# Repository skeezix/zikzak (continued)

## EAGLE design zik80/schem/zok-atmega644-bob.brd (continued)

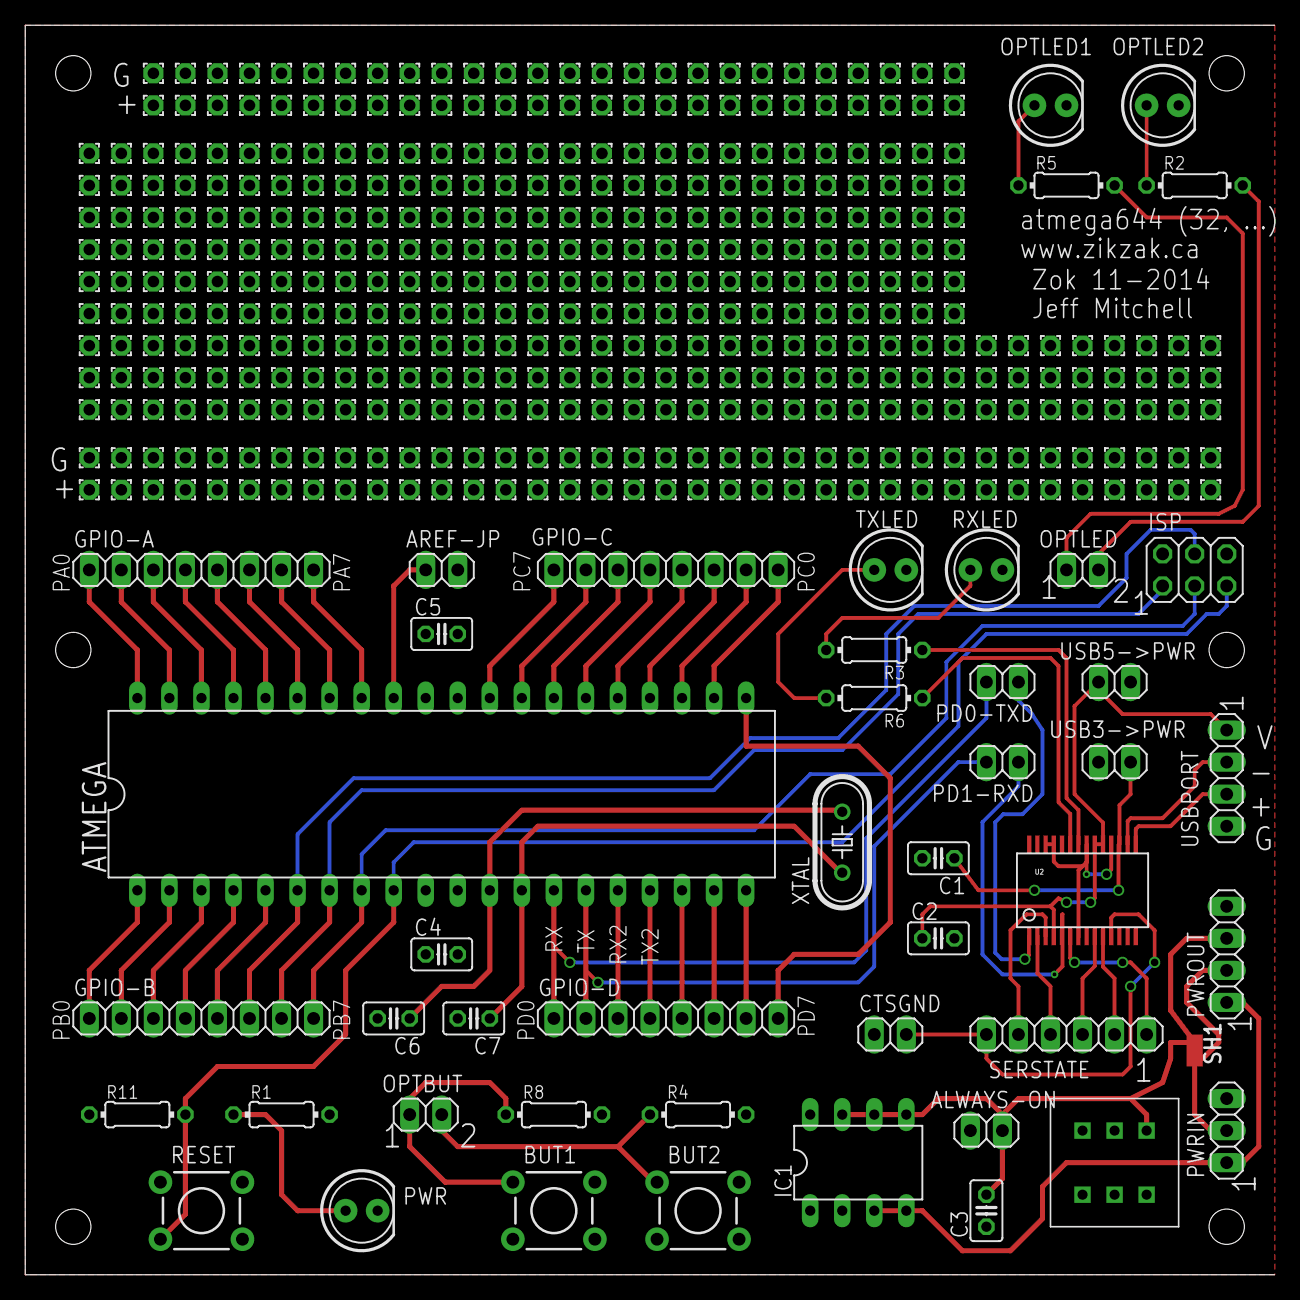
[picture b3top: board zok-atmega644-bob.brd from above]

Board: 2 copper layers, 99.1 x 99.1 mm, 447 parts (0 on the bottom side), 64 nets.

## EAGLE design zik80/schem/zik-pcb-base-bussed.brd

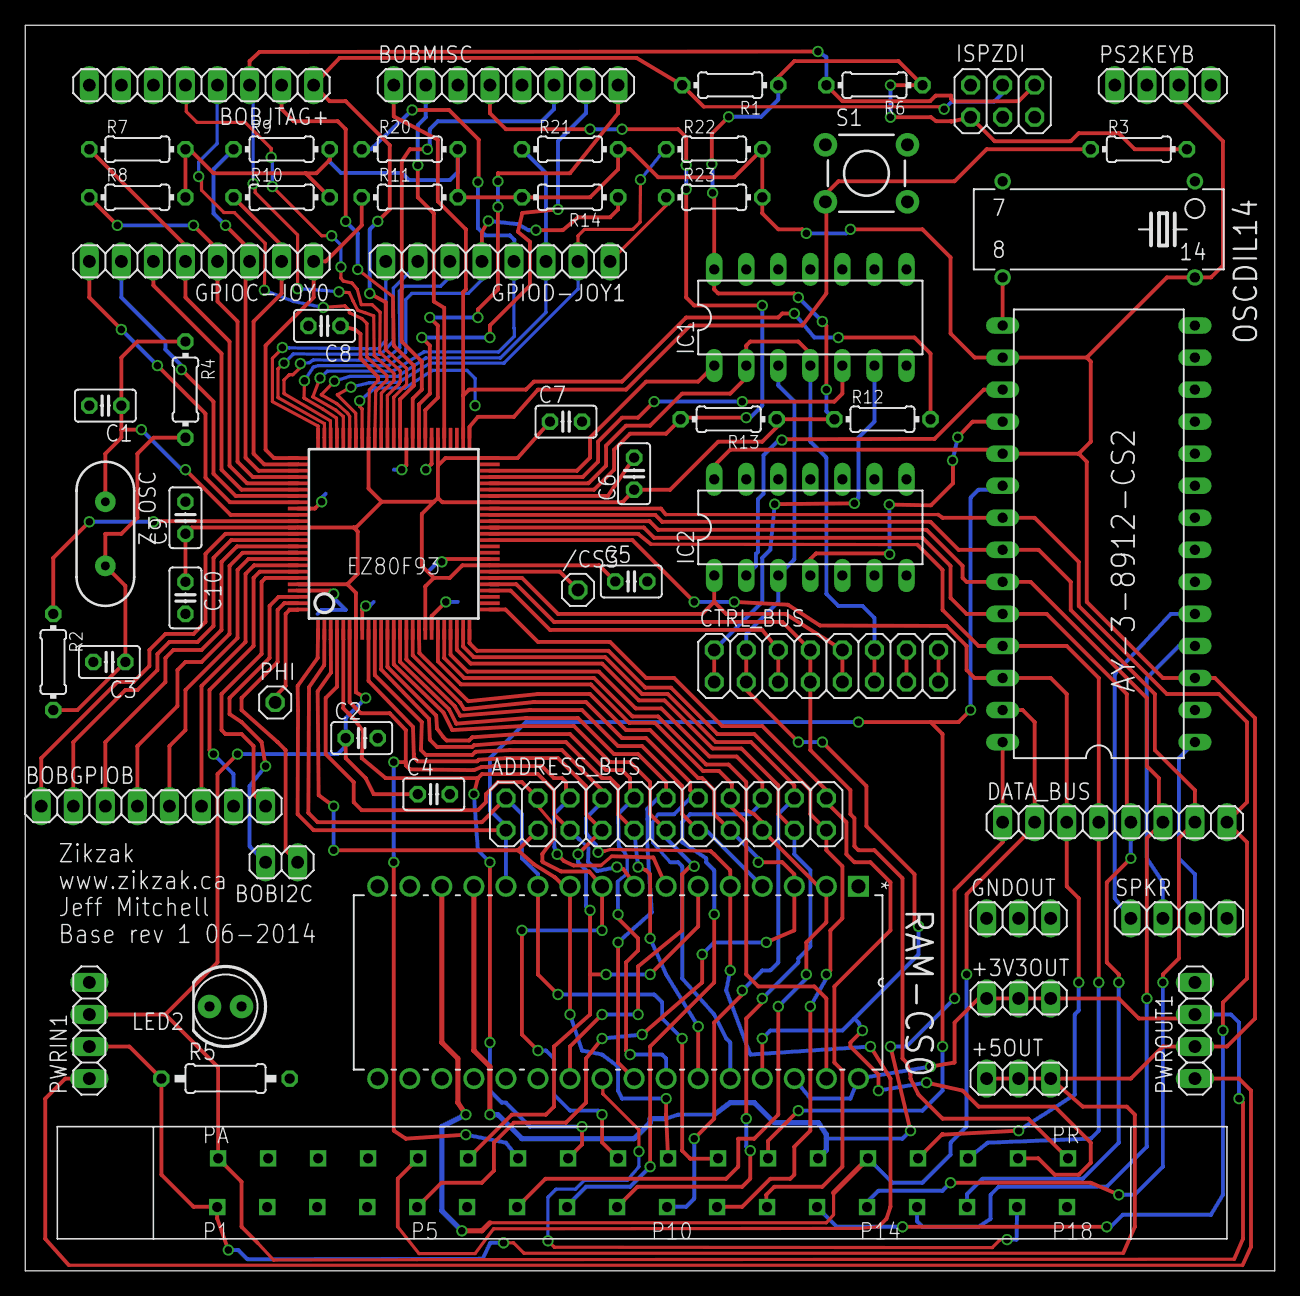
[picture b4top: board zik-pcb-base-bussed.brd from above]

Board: 2 copper layers, 99.0 x 98.7 mm, 57 parts (0 on the bottom side), 94 nets.

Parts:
+3V3OUT, +5OUT: 1X03
/CS3: 1X01
ADDRESS_BUS: 2X11
AY-3-8912-CS2: DIL28
BOBGPIOB: 1X08
BOBI2C: 1X02
BOBJTAG+: 1X08
BOBMISC: 1X08
C1, C3: 22pF; C025-025X050
C2, C4, C5, C6, C7, C8, C9, C10: .1uF; C025-025X050
CART-CS1: ZIKCART36; ZIKCARTSLOT
CTRL_BUS: 2X08
DATA_BUS: 1X08
EZ80F93: SQFP-S-14X14-100
GNDOUT: 1X03
GPIOC-JOY0: 1X08
GPIOD-JOY1: 1X08
IC1: 7432N; DIL14
IC2: 7404N; DIL14
ISPZDI: 2X03
LED2: LED5MM
OSCDIL14: 2.5MHz; SG51
PHI: 1X01
PS2KEYB: 1X04
PWRIN1: 1X04
PWROUT1: 1X04
R1, R3, R6, R7, R8, R9, R10, R11, R12, R13, R14, R20, R21, R22, R23: 10K; 0204/7
R2: 220 O; 0204/7
R4: 100K; 0204/7
R5: 1K; 0207/10
RAM-CS0: AS6C1008-55PCN; DIP254P1524X393-32
S1: SWITCH-MOMENTARY-2PTH; TACTILE-PTH
SPKR: 1X04
Z-OSC: 20Mhz; HC49US

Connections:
+3V3: +3V3OUT.1, +3V3OUT.2, +3V3OUT.3, C2.1, C4.1, C5.1, C6.1, C7.1, C8.1, C9.1, C10.1, CART-CS1.PA, EZ80F93.7, EZ80F93.18, EZ80F93.33, EZ80F93.43, EZ80F93.50, EZ80F93.56, EZ80F93.67, EZ80F93.87, EZ80F93.96, IC1.14, ISPZDI.1, PWRIN1.3, PWROUT1.3, R1.1, R3.2, R6.1, R12.1, R13.1, RAM-CS0.30, RAM-CS0.32
+5V: +5OUT.1, +5OUT.2, +5OUT.3, AY-3-8912-CS2.3, AY-3-8912-CS2.16, AY-3-8912-CS2.19, CART-CS1.P1, IC2.14, OSCDIL14.14, PS2KEYB.3, PWRIN1.2, PWROUT1.2, R5.1, R7.2, R8.2, R9.2, R10.2, R11.2, R14.2, R20.2, R21.2, R22.2, R23.2
+CS2: AY-3-8912-CS2.17, IC2.2
+MEMWRITE: AY-3-8912-CS2.18, IC2.4
/BUSACK: CTRL_BUS.15, CTRL_BUS.16, EZ80F93.54
/BUSREQ: CTRL_BUS.13, CTRL_BUS.14, EZ80F93.53
/CS0: CTRL_BUS.5, CTRL_BUS.6, EZ80F93.29, RAM-CS0.22
/CS1: CART-CS1.PR, CTRL_BUS.7, CTRL_BUS.8, EZ80F93.30
/CS2: CTRL_BUS.9, CTRL_BUS.10, EZ80F93.31, IC2.1
/CS3: /CS3.1, EZ80F93.32
/IOREQ: BOBMISC.4, EZ80F93.45, R13.2
/MEMREAD: CART-CS1.P17, CTRL_BUS.1, CTRL_BUS.2, IC1.6, RAM-CS0.24
/MEMWRITE: CART-CS1.PQ, CTRL_BUS.3, CTRL_BUS.4, IC1.3, IC2.3, RAM-CS0.29
/MREQ: CTRL_BUS.11, CTRL_BUS.12, EZ80F93.46, IC1.2, IC1.4
/RD: EZ80F93.47, IC1.5
/WR: EZ80F93.48, IC1.1
A0: ADDRESS_BUS.1, AY-3-8912-CS2.20, CART-CS1.PL, EZ80F93.1, RAM-CS0.12
A1: ADDRESS_BUS.2, CART-CS1.PK, EZ80F93.2, RAM-CS0.11
A2: ADDRESS_BUS.3, CART-CS1.PJ, EZ80F93.3, RAM-CS0.10
A3: ADDRESS_BUS.4, CART-CS1.PI, EZ80F93.4, RAM-CS0.9
A4: ADDRESS_BUS.5, CART-CS1.PH, EZ80F93.5, RAM-CS0.8
A5: ADDRESS_BUS.6, CART-CS1.PG, EZ80F93.6, RAM-CS0.7
A6: ADDRESS_BUS.7, CART-CS1.PF, EZ80F93.9, RAM-CS0.6
A7: ADDRESS_BUS.8, CART-CS1.PE, EZ80F93.10, RAM-CS0.5
A8: ADDRESS_BUS.9, CART-CS1.PD, EZ80F93.11, RAM-CS0.27
A9: ADDRESS_BUS.10, CART-CS1.PC, EZ80F93.12, RAM-CS0.26
A10: ADDRESS_BUS.11, CART-CS1.PB, EZ80F93.13, RAM-CS0.23
A11: ADDRESS_BUS.12, CART-CS1.P2, EZ80F93.14, RAM-CS0.25
A12: ADDRESS_BUS.13, CART-CS1.P3, EZ80F93.15, RAM-CS0.4
A13: ADDRESS_BUS.14, CART-CS1.P4, EZ80F93.16, RAM-CS0.28
A14: ADDRESS_BUS.15, CART-CS1.P5, EZ80F93.17, RAM-CS0.3
A15: ADDRESS_BUS.16, CART-CS1.P6, EZ80F93.20, RAM-CS0.31
A16: ADDRESS_BUS.17, CART-CS1.P7, EZ80F93.21, RAM-CS0.2
A17: ADDRESS_BUS.18, CART-CS1.P8, EZ80F93.22
A18: ADDRESS_BUS.19, CART-CS1.P9, EZ80F93.23
A19: ADDRESS_BUS.20, CART-CS1.P10, EZ80F93.24
A20: ADDRESS_BUS.21, CART-CS1.P11, EZ80F93.25
A21: ADDRESS_BUS.22, CART-CS1.P12, EZ80F93.26
D0: AY-3-8912-CS2.28, CART-CS1.PM, DATA_BUS.1, EZ80F93.35, RAM-CS0.13
D1: AY-3-8912-CS2.27, CART-CS1.PN, DATA_BUS.2, EZ80F93.36, RAM-CS0.14
D2: AY-3-8912-CS2.26, CART-CS1.PO, DATA_BUS.3, EZ80F93.37, RAM-CS0.15
D3: AY-3-8912-CS2.25, CART-CS1.PP, DATA_BUS.4, EZ80F93.38, RAM-CS0.17
D4: AY-3-8912-CS2.24, CART-CS1.P16, DATA_BUS.5, EZ80F93.39, RAM-CS0.18
D5: AY-3-8912-CS2.23, CART-CS1.P15, DATA_BUS.6, EZ80F93.40, RAM-CS0.19
D6: AY-3-8912-CS2.22, CART-CS1.P14, DATA_BUS.7, EZ80F93.41, RAM-CS0.20
D7: AY-3-8912-CS2.21, CART-CS1.P13, DATA_BUS.8, EZ80F93.42, RAM-CS0.21
GND: AY-3-8912-CS2.6, C1.2, C2.2, C3.2, C4.2, C5.2, C6.2, C7.2, C8.2, C9.2, C10.2, CART-CS1.P18, EZ80F93.8, EZ80F93.19, EZ80F93.34, EZ80F93.44, EZ80F93.57, EZ80F93.61, EZ80F93.84, EZ80F93.97, GNDOUT.1, GNDOUT.2, GNDOUT.3, IC1.7, IC1.9, IC1.10, IC1.12, IC1.13, IC2.5, IC2.7, IC2.9, IC2.11, IC2.13, ISPZDI.3, ISPZDI.5, LED2.K, OSCDIL14.7, PS2KEYB.2, PWRIN1.4, PWROUT1.4, RAM-CS0.16, S1.1, SPKR.4
HALT_SLP: BOBMISC.2, EZ80F93.55
unnamed: C3.1, R2.2, R4.2, Z-OSC.2
unnamed: LED2.A, R5.2
unnamed: AY-3-8912-CS2.4, SPKR.2
unnamed: AY-3-8912-CS2.1, SPKR.3
unnamed: AY-3-8912-CS2.5, SPKR.1
unnamed: AY-3-8912-CS2.15, OSCDIL14.8
NMI: BOBMISC.1, EZ80F93.52, R12.2
NRST: EZ80F93.51, R3.1, S1.3
PB0: BOBGPIOB.1, EZ80F93.88
PB1: BOBGPIOB.2, EZ80F93.89
PB2: BOBGPIOB.3, EZ80F93.90
PB3: BOBGPIOB.4, EZ80F93.91
PB4: BOBGPIOB.5, EZ80F93.92
PB5: BOBGPIOB.6, EZ80F93.93
PB6: BOBGPIOB.7, EZ80F93.94
PB7: BOBGPIOB.8, EZ80F93.95
PC0: EZ80F93.76, GPIOC-JOY0.1, R11.1
PC1: EZ80F93.77, GPIOC-JOY0.2, R10.1
PC2: EZ80F93.78, GPIOC-JOY0.3, R9.1
PC3: EZ80F93.79, GPIOC-JOY0.4, R8.1
PC4: EZ80F93.80, GPIOC-JOY0.5, R7.1
PC5: EZ80F93.81, GPIOC-JOY0.6
PC6: EZ80F93.82, GPIOC-JOY0.7
PC7: EZ80F93.83, GPIOC-JOY0.8
PD0: EZ80F93.68, GPIOD-JOY1.1, R23.1
PD1: EZ80F93.69, GPIOD-JOY1.2, R22.1
PD2: EZ80F93.70, GPIOD-JOY1.3, R21.1
PD3: EZ80F93.71, GPIOD-JOY1.4, R20.1
PD4: EZ80F93.72, GPIOD-JOY1.5, R14.1
PD5: EZ80F93.73, GPIOD-JOY1.6
PD6: EZ80F93.74, GPIOD-JOY1.7, PS2KEYB.4
PD7: EZ80F93.75, GPIOD-JOY1.8, PS2KEYB.1
PHI: EZ80F93.100, PHI.1
RTC_VDD: BOBMISC.6, EZ80F93.60
RTC_XIN: BOBMISC.8, EZ80F93.58
RTC_XOUT: BOBMISC.7, EZ80F93.59
SCL: BOBI2C.1, EZ80F93.99
SDA: BOBI2C.2, EZ80F93.98
TCK_ZCL: BOBJTAG+.1, EZ80F93.63, ISPZDI.4, R1.2
TDI_ZDA: BOBJTAG+.3, EZ80F93.65, ISPZDI.6, R6.2
TDO: BOBJTAG+.4, EZ80F93.66
TMS: BOBJTAG+.2, EZ80F93.62
TRIGOUT: BOBJTAG+.5, EZ80F93.64
VCC: PWRIN1.1, PWROUT1.1
XIN: C1.1, EZ80F93.85, R4.1, Z-OSC.1
XOUT: EZ80F93.86, R2.1

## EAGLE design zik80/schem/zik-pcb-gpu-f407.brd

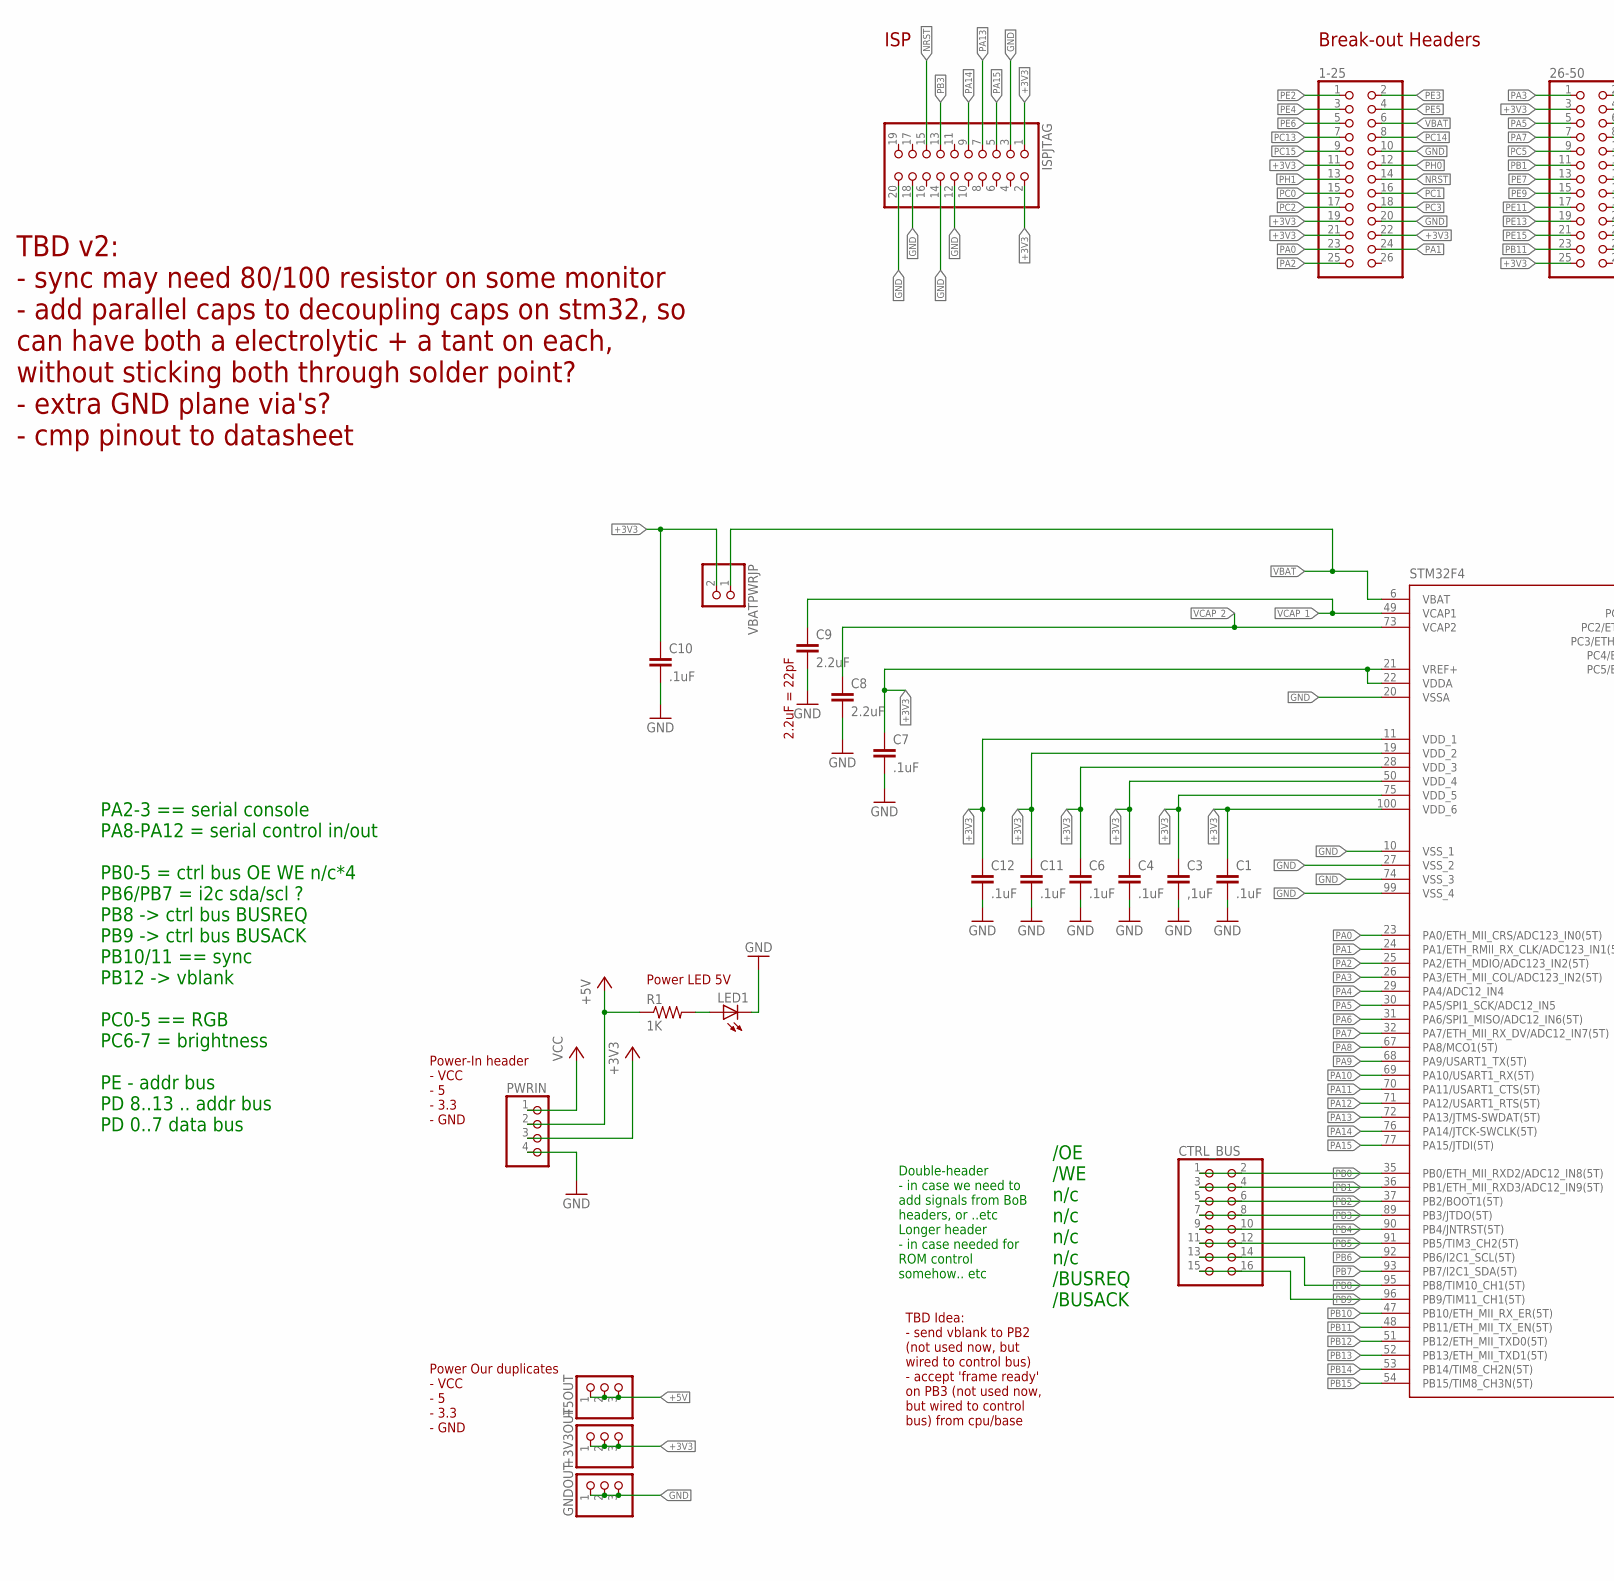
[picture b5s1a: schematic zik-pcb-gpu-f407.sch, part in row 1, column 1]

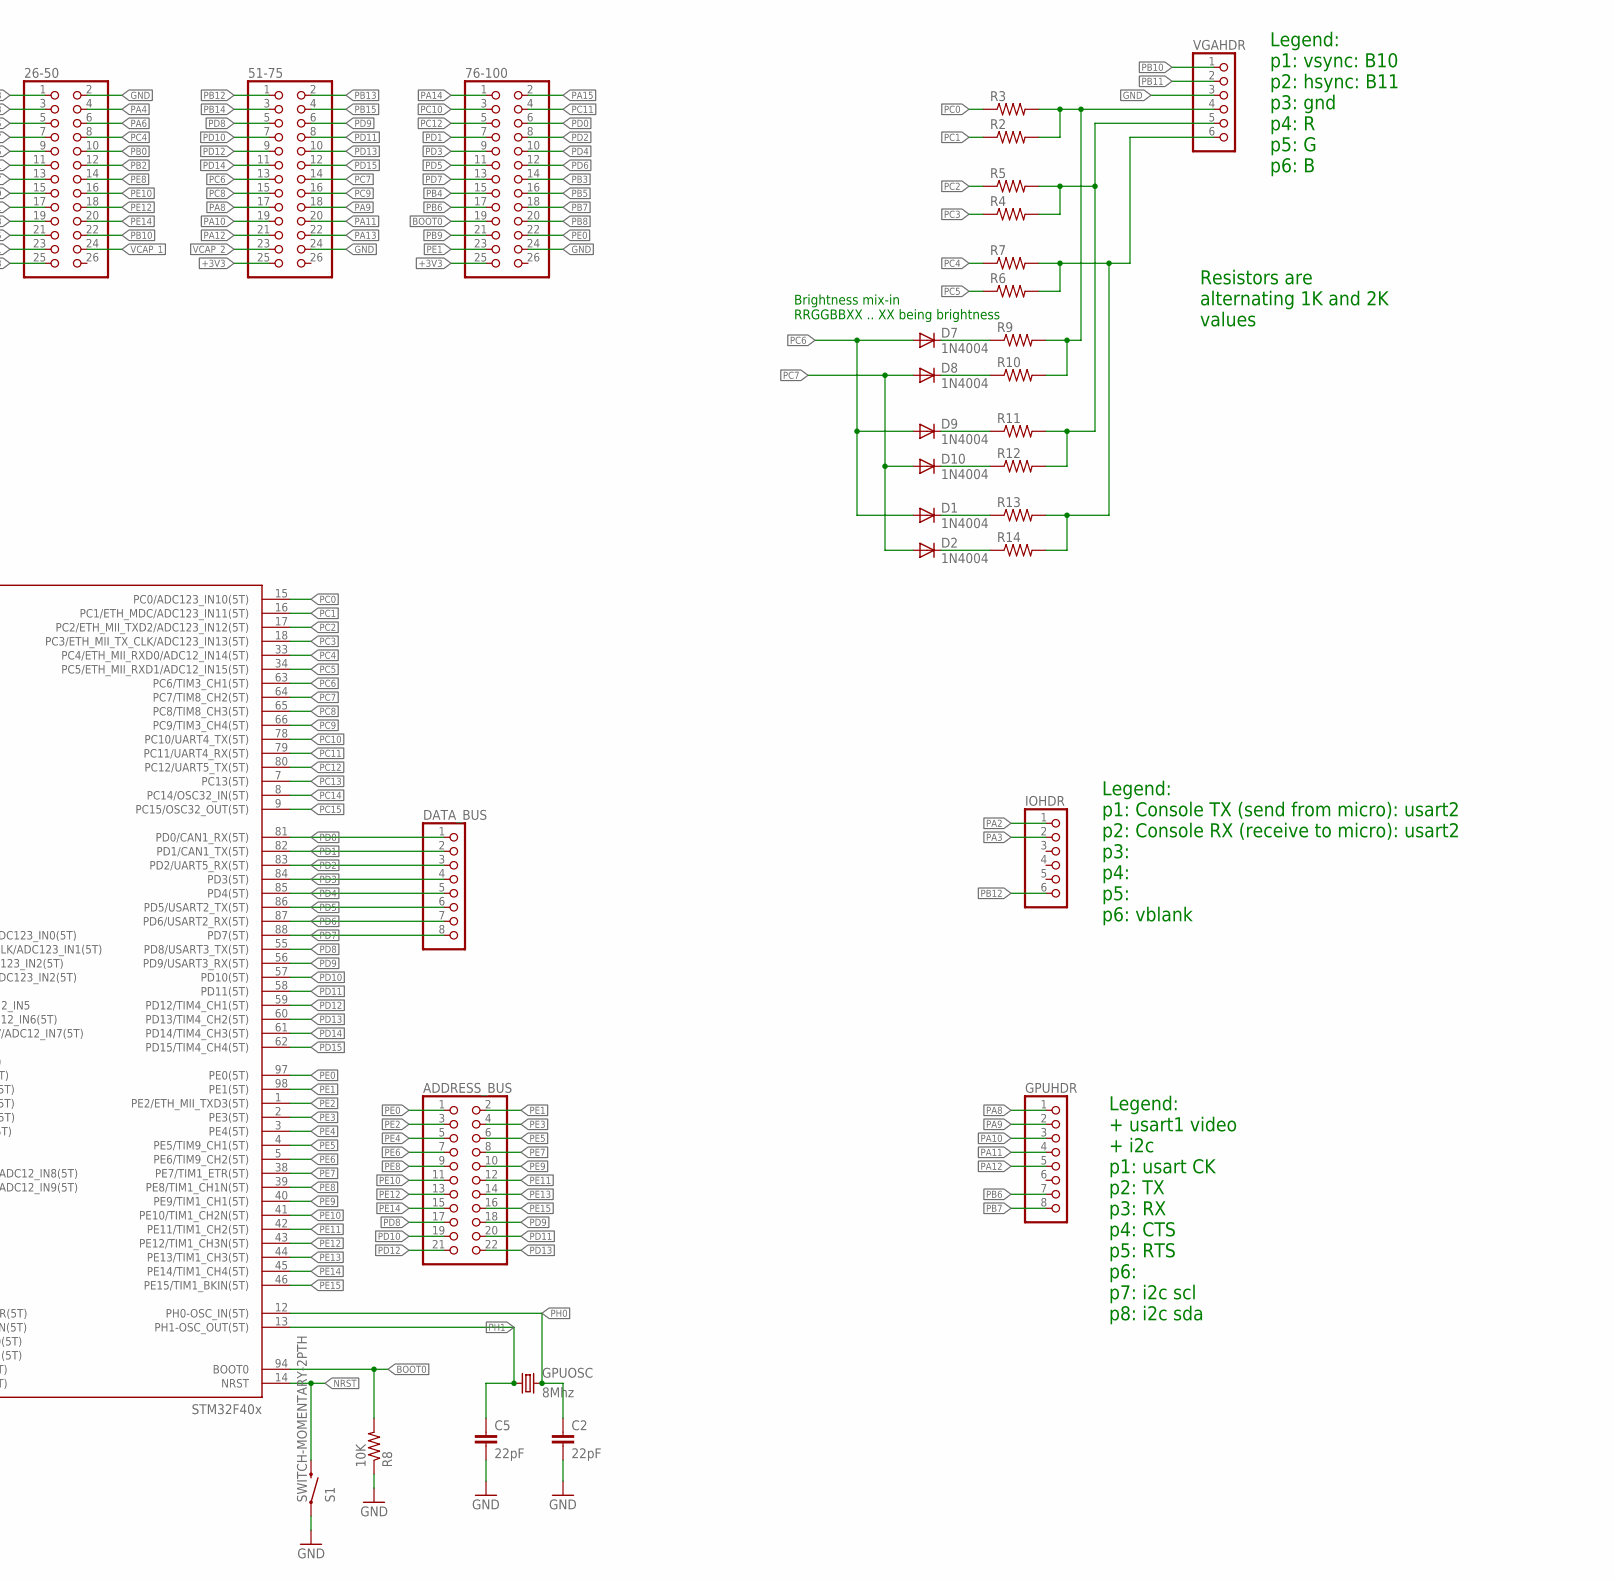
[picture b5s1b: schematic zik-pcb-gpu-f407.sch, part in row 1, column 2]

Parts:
1-25, 26-50, 51-75, 76-100: PINHD-2X13; 2X13
+3V3OUT, +5OUT: PINHD-1X3; 1X03
ADDRESS_BUS: PINHD-2X11; 2X11
C1, C4, C6, C7, C10, C11, C12: .1uF; C025-025X050
C2, C5: 22pF; C025-025X050
C3: ,1uF; C025-025X050
C8, C9: 2.2uF; C025-025X050
CTRL_BUS: PINHD-2X8; 2X08
D1, D2, D7, D8, D9, D10: 1N4004; DO41-10
DATA_BUS: PINHD-1X8; 1X08
GNDOUT: PINHD-1X3; 1X03
GPUHDR: PINHD-1X8; 1X08
GPUOSC: 8Mhz; HC49US
IOHDR: PINHD-1X6; 1X06
ISPJTAG: PINHD-2X10; 2X10
LED1: LED5MM
PWRIN: PINHD-1X4; 1X04
R1: 1K; 0207/10
R2, R3, R4, R5, R6, R7, R9, R10, R11, R12, R13, R14: R-US_0207/10; 0207/10
R8: 10K; 0207/10
S1: SWITCH-MOMENTARY-2PTH; TACTILE-PTH
STM32F4: STM32F407V; TQFP100
VBATPWRJP: PINHD-1X2; 1X02
VGAHDR: PINHD-1X6; 1X06

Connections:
+3V3: 1-25.11, 1-25.19, 1-25.21, 1-25.22, 26-50.3, 26-50.25, 51-75.25, 76-100.25, +3V3OUT.1, +3V3OUT.2, +3V3OUT.3, C1.1, C3.1, C4.1, C6.1, C7.1, C10.1, C11.1, C12.1, ISPJTAG.1, ISPJTAG.2, PWRIN.3, STM32F4.11 (VDD_1), STM32F4.19 (VDD_2), STM32F4.21 (VREF+), STM32F4.22 (VDDA), STM32F4.28 (VDD_3), STM32F4.50 (VDD_4), STM32F4.75 (VDD_5), STM32F4.100 (VDD_6), VBATPWRJP.2
+5V: +5OUT.1, +5OUT.2, +5OUT.3, PWRIN.2, R1.1
BOOT0: 76-100.19, R8.2, STM32F4.94 (BOOT0)
GND: 1-25.10, 1-25.20, 26-50.2, 51-75.24, 76-100.24, C1.2, C2.2, C3.2, C4.2, C5.2, C6.2, C7.2, C8.2, C9.2, C10.2, C11.2, C12.2, GNDOUT.1, GNDOUT.2, GNDOUT.3, ISPJTAG.3, ISPJTAG.12, ISPJTAG.14, ISPJTAG.18, ISPJTAG.20, LED1.K (C), PWRIN.4, R8.1, S1.1, STM32F4.10 (VSS_1), STM32F4.20 (VSSA), STM32F4.27 (VSS_2), STM32F4.74 (VSS_3), STM32F4.99 (VSS_4), VGAHDR.3
unnamed: LED1.A, R1.2
unnamed: D7.C, R9.1
unnamed: R4.2, R5.2, R11.2, R12.2, VGAHDR.5
unnamed: D8.C, R10.1
unnamed: R6.2, R7.2, R13.2, R14.2, VGAHDR.6
unnamed: R2.2, R3.2, R9.2, R10.2, VGAHDR.4
unnamed: D9.C, R11.1
unnamed: D10.C, R12.1
unnamed: D1.C, R13.1
unnamed: D2.C, R14.1
NRST: 1-25.14, ISPJTAG.15, S1.3 (2), STM32F4.14 (NRST)
PA0: 1-25.23, STM32F4.23 (PA0/ETH_MII_CRS/ADC123_IN0(5T))
PA1: 1-25.24, STM32F4.24 (PA1/ETH_RMII_RX_CLK/ADC123_IN1(5T))
PA2: 1-25.25, IOHDR.1, STM32F4.25 (PA2/ETH_MDIO/ADC123_IN2(5T))
PA3: 26-50.1, IOHDR.2, STM32F4.26 (PA3/ETH_MII_COL/ADC123_IN2(5T))
PA4: 26-50.4, STM32F4.29 (PA4/ADC12_IN4)
PA5: 26-50.5, STM32F4.30 (PA5/SPI1_SCK/ADC12_IN5)
PA6: 26-50.6, STM32F4.31 (PA6/SPI1_MISO/ADC12_IN6(5T))
PA7: 26-50.7, STM32F4.32 (PA7/ETH_MII_RX_DV/ADC12_IN7(5T))
PA8: 51-75.17, GPUHDR.1, STM32F4.67 (PA8/MCO1(5T))
PA9: 51-75.18, GPUHDR.2, STM32F4.68 (PA9/USART1_TX(5T))
PA10: 51-75.19, GPUHDR.3, STM32F4.69 (PA10/USART1_RX(5T))
PA11: 51-75.20, GPUHDR.4, STM32F4.70 (PA11/USART1_CTS(5T))
PA12: 51-75.21, GPUHDR.5, STM32F4.71 (PA12/USART1_RTS(5T))
PA13: 51-75.22, ISPJTAG.7, STM32F4.72 (PA13/JTMS-SWDAT(5T))
PA14: 76-100.1, ISPJTAG.9, STM32F4.76 (PA14/JTCK-SWCLK(5T))
PA15: 76-100.2, ISPJTAG.5, STM32F4.77 (PA15/JTDI(5T))
PB0: 26-50.10, CTRL_BUS.1, CTRL_BUS.2, STM32F4.35 (PB0/ETH_MII_RXD2/ADC12_IN8(5T))
PB1: 26-50.11, CTRL_BUS.3, CTRL_BUS.4, STM32F4.36 (PB1/ETH_MII_RXD3/ADC12_IN9(5T))
PB2: 26-50.12, CTRL_BUS.5, CTRL_BUS.6, STM32F4.37 (PB2/BOOT1(5T))
PB3: 76-100.14, CTRL_BUS.7, CTRL_BUS.8, ISPJTAG.13, STM32F4.89 (PB3/JTDO(5T))
PB4: 76-100.15, CTRL_BUS.9, CTRL_BUS.10, STM32F4.90 (PB4/JNTRST(5T))
PB5: 76-100.16, CTRL_BUS.11, CTRL_BUS.12, STM32F4.91 (PB5/TIM3_CH2(5T))
PB6: 76-100.17, GPUHDR.7, STM32F4.92 (PB6/I2C1_SCL(5T))
PB7: 76-100.18, GPUHDR.8, STM32F4.93 (PB7/I2C1_SDA(5T))
PB8: 76-100.20, CTRL_BUS.13, CTRL_BUS.14, STM32F4.95 (PB8/TIM10_CH1(5T))
PB9: 76-100.21, CTRL_BUS.15, CTRL_BUS.16, STM32F4.96 (PB9/TIM11_CH1(5T))
PB10: 26-50.22, STM32F4.47 (PB10/ETH_MII_RX_ER(5T)), VGAHDR.1
PB11: 26-50.23, STM32F4.48 (PB11/ETH_MII_TX_EN(5T)), VGAHDR.2
PB12: 51-75.1, IOHDR.6, STM32F4.51 (PB12/ETH_MII_TXD0(5T))
PB13: 51-75.2, STM32F4.52 (PB13/ETH_MII_TXD1(5T))
PB14: 51-75.3, STM32F4.53 (PB14/TIM8_CH2N(5T))
PB15: 51-75.4, STM32F4.54 (PB15/TIM8_CH3N(5T))
PC0: 1-25.15, R3.1, STM32F4.15 (PC0/ADC123_IN10(5T))
PC1: 1-25.16, R2.1, STM32F4.16 (PC1/ETH_MDC/ADC123_IN11(5T))
PC2: 1-25.17, R5.1, STM32F4.17 (PC2/ETH_MII_TXD2/ADC123_IN12(5T))
PC3: 1-25.18, R4.1, STM32F4.18 (PC3/ETH_MII_TX_CLK/ADC123_IN13(5T))
PC4: 26-50.8, R7.1, STM32F4.33 (PC4/ETH_MII_RXD0/ADC12_IN14(5T))
PC5: 26-50.9, R6.1, STM32F4.34 (PC5/ETH_MII_RXD1/ADC12_IN15(5T))
PC6: 51-75.13, D1.A, D7.A, D9.A, STM32F4.63 (PC6/TIM3_CH1(5T))
PC7: 51-75.14, D2.A, D8.A, D10.A, STM32F4.64 (PC7/TIM8_CH2(5T))
PC8: 51-75.15, STM32F4.65 (PC8/TIM8_CH3(5T))
PC9: 51-75.16, STM32F4.66 (PC9/TIM3_CH4(5T))
PC10: 76-100.3, STM32F4.78 (PC10/UART4_TX(5T))
PC11: 76-100.4, STM32F4.79 (PC11/UART4_RX(5T))
PC12: 76-100.5, STM32F4.80 (PC12/UART5_TX(5T))
PC13: 1-25.7, STM32F4.7 (PC13(5T))
PC14: 1-25.8, STM32F4.8 (PC14/OSC32_IN(5T))
PC15: 1-25.9, STM32F4.9 (PC15/OSC32_OUT(5T))
PD0: 76-100.6, DATA_BUS.1, STM32F4.81 (PD0/CAN1_RX(5T))
PD1: 76-100.7, DATA_BUS.2, STM32F4.82 (PD1/CAN1_TX(5T))
PD2: 76-100.8, DATA_BUS.3, STM32F4.83 (PD2/UART5_RX(5T))
PD3: 76-100.9, DATA_BUS.4, STM32F4.84 (PD3(5T))
PD4: 76-100.10, DATA_BUS.5, STM32F4.85 (PD4(5T))
PD5: 76-100.11, DATA_BUS.6, STM32F4.86 (PD5/USART2_TX(5T))
PD6: 76-100.12, DATA_BUS.7, STM32F4.87 (PD6/USART2_RX(5T))
PD7: 76-100.13, DATA_BUS.8, STM32F4.88 (PD7(5T))
PD8: 51-75.5, ADDRESS_BUS.17, STM32F4.55 (PD8/USART3_TX(5T))
PD9: 51-75.6, ADDRESS_BUS.18, STM32F4.56 (PD9/USART3_RX(5T))
PD10: 51-75.7, ADDRESS_BUS.19, STM32F4.57 (PD10(5T))
PD11: 51-75.8, ADDRESS_BUS.20, STM32F4.58 (PD11(5T))
PD12: 51-75.9, ADDRESS_BUS.21, STM32F4.59 (PD12/TIM4_CH1(5T))
PD13: 51-75.10, ADDRESS_BUS.22, STM32F4.60 (PD13/TIM4_CH2(5T))
PD14: 51-75.11, STM32F4.61 (PD14/TIM4_CH3(5T))
PD15: 51-75.12, STM32F4.62 (PD15/TIM4_CH4(5T))
PE0: 76-100.22, ADDRESS_BUS.1, STM32F4.97 (PE0(5T))
PE1: 76-100.23, ADDRESS_BUS.2, STM32F4.98 (PE1(5T))
PE2: 1-25.1, ADDRESS_BUS.3, STM32F4.1 (PE2/ETH_MII_TXD3(5T))
PE3: 1-25.2, ADDRESS_BUS.4, STM32F4.2 (PE3(5T))
PE4: 1-25.3, ADDRESS_BUS.5, STM32F4.3 (PE4(5T))
PE5: 1-25.4, ADDRESS_BUS.6, STM32F4.4 (PE5/TIM9_CH1(5T))
PE6: 1-25.5, ADDRESS_BUS.7, STM32F4.5 (PE6/TIM9_CH2(5T))
PE7: 26-50.13, ADDRESS_BUS.8, STM32F4.38 (PE7/TIM1_ETR(5T))
PE8: 26-50.14, ADDRESS_BUS.9, STM32F4.39 (PE8/TIM1_CH1N(5T))
PE9: 26-50.15, ADDRESS_BUS.10, STM32F4.40 (PE9/TIM1_CH1(5T))
PE10: 26-50.16, ADDRESS_BUS.11, STM32F4.41 (PE10/TIM1_CH2N(5T))
PE11: 26-50.17, ADDRESS_BUS.12, STM32F4.42 (PE11/TIM1_CH2(5T))
PE12: 26-50.18, ADDRESS_BUS.13, STM32F4.43 (PE12/TIM1_CH3N(5T))
PE13: 26-50.19, ADDRESS_BUS.14, STM32F4.44 (PE13/TIM1_CH3(5T))
PE14: 26-50.20, ADDRESS_BUS.15, STM32F4.45 (PE14/TIM1_CH4(5T))
PE15: 26-50.21, ADDRESS_BUS.16, STM32F4.46 (PE15/TIM1_BKIN(5T))
PH0: 1-25.12, C2.1, GPUOSC.2, STM32F4.12 (PH0-OSC_IN(5T))
PH1: 1-25.13, C5.1, GPUOSC.1, STM32F4.13 (PH1-OSC_OUT(5T))
VBAT: 1-25.6, STM32F4.6 (VBAT), VBATPWRJP.1
VCAP_1: 26-50.24, C9.1, STM32F4.49 (VCAP1)
VCAP_2: 51-75.23, C8.1, STM32F4.73 (VCAP2)
VCC: PWRIN.1

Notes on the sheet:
Power-In header - VCC - 5 - 3.3 - GND
Break-out Headers
ISP
Power Our duplicates - VCC - 5 - 3.3 - GND
2.2uF = 22pF
TBD v2: - sync may need 80/100 resistor on some monitor - add parallel caps to decoupling caps on stm32, so can have both a electrolytic + a tant on each, without sticking both through solder point? - extra GND plane via's? - cmp pinout to datasheet
Power LED 5V
Legend: p1: vsync: B10 p2: hsync: B11 p3: gnd p4: R p5: G p6: B
PA2-3 == serial console PA8-PA12 = serial control in/out PB0-5 = ctrl bus OE WE n/c*4 PB6/PB7 = i2c sda/scl ? PB8 -> ctrl bus BUSREQ PB9 -> ctrl bus BUSACK PB10/11 == sync PB12 -> vblank PC0-5 == RGB PC6-7 = brightness PE - addr bus PD 8..13 .. addr bus PD 0..7 data bus
Legend: p1: Console TX (send from micro): usart2 p2: Console RX (receive to micro): usart2 p3: p4: p5: p6: vblank
Legend: + usart1 video + i2c p1: usart CK p2: TX p3: RX p4: CTS p5: RTS p6: p7: i2c scl p8: i2c sda
Brightness mix-in RRGGBBXX .. XX being brightness
Resistors are alternating 1K and 2K values
/OE /WE n/c n/c n/c n/c /BUSREQ /BUSACK
Double-header - in case we need to add signals from BoB headers, or ..etc Longer header - in case needed for ROM control somehow.. etc
TBD Idea: - send vblank to PB2 (not used now, but wired to control bus) - accept 'frame ready' on PB3 (not used now, but wired to control bus) from cpu/base

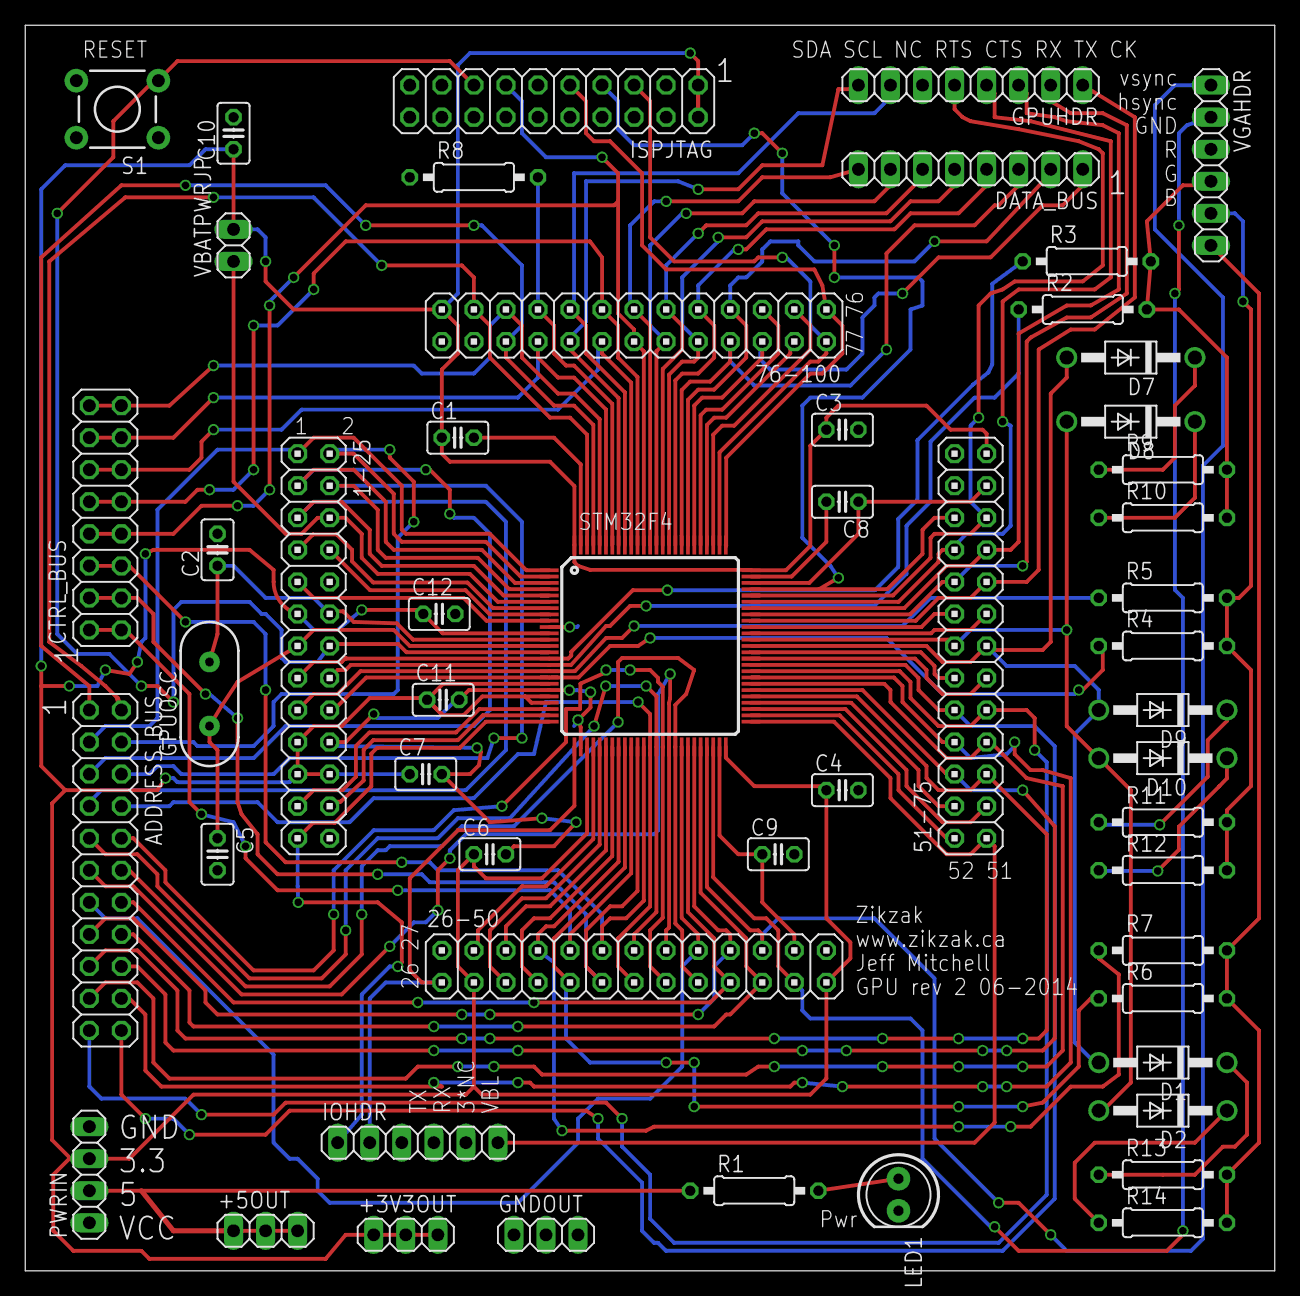
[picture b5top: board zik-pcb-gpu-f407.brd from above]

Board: 2 copper layers, 99.0 x 98.7 mm, 52 parts (0 on the bottom side), 100 nets.

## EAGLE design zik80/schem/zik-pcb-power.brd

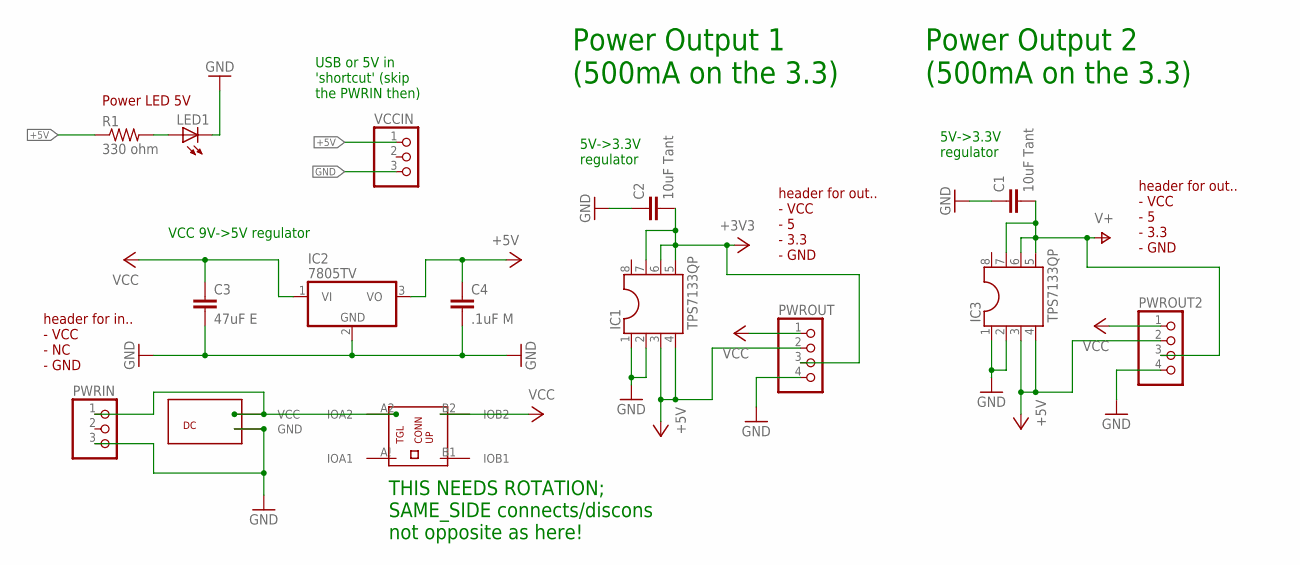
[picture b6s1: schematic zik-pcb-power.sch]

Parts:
C1, C2: 10uF Tant; C025-025X050
C3: 47uF E; C025-025X050
C4: .1uF M; C025-025X050
IC1, IC3: TPS7133QP; DIL08
IC2: 7805TV; TO220V
LED1: LED5MM
PWRIN: PINHD-1X3; 1X03
PWROUT, PWROUT2: PINHD-1X4; 1X04
R1: 330 ohm; 0207/10
U$1: DCJACKZIK
U$2: TOGGLE-CYAN-L-ZIK; TOGGLE-CYAN-LG-ZIK
VCCIN: PINHD-1X3; 1X03

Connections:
+3V3: C2.2, IC1.5, IC1.6, IC1.7, PWROUT.3
+5V: C4.1, IC1.3, IC1.4, IC2.3 (VO), IC3.3, IC3.4, PWROUT.2, PWROUT2.2, R1.1, VCCIN.1
GND: C1.1, C2.1, C3.2, C4.2, IC1.1, IC1.2, IC2.2 (GND), IC3.1, IC3.2, LED1.K (C), PWRIN.3, PWROUT.4, PWROUT2.4, U$1.JACKET (GND), VCCIN.3
unnamed: PWRIN.1, U$1.CPIN (VCC), U$2.A2 (IOA2)
unnamed: LED1.A, R1.2
V+: C1.2, IC3.5, IC3.6, IC3.7, PWROUT2.3
VCC: C3.1, IC2.1 (VI), PWROUT.1, PWROUT2.1, U$2.B2 (IOB2)

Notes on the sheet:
5V->3.3V regulator
VCC 9V->5V regulator
header for out.. - VCC - 5 - 3.3 - GND
header for in.. - VCC - NC - GND
Power Output 1 (500mA on the 3.3)
Power Output 2 (500mA on the 3.3)
USB or 5V in 'shortcut' (skip the PWRIN then)
Power LED 5V
THIS NEEDS ROTATION; SAME_SIDE connects/discons not opposite as here!

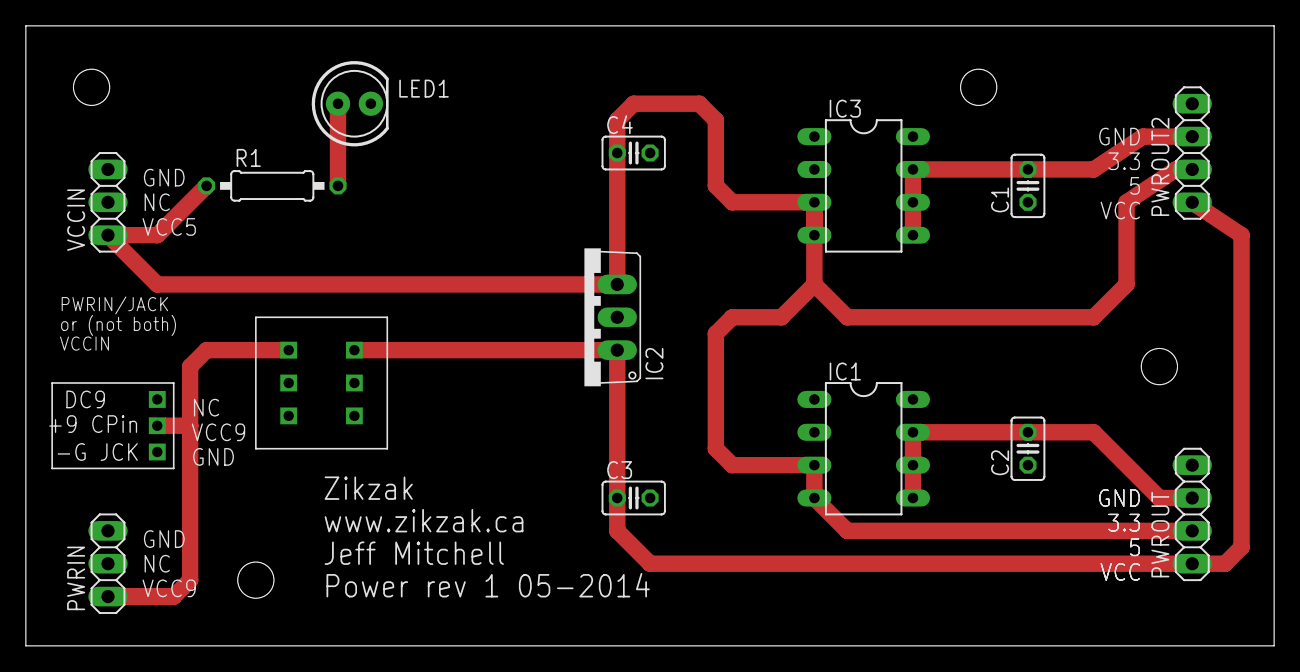
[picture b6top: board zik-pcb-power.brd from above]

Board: 2 copper layers, 96.5 x 47.9 mm, 15 parts (0 on the bottom side), 7 nets.
